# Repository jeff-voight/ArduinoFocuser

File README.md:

# ArduinoFocuser
My homemade Arduino Focuser

### Parts List
|ID				|#	|Name					|Type								|Module										|Description|
| ---			| ---	| ---					| ---								| ---										| ---										|
|A1				|1	|Arduino_UNO_R3			|MCU_Module:Arduino_UNO_R3			|Module:Arduino_UNO_R3						|Arduino UNO Microcontroller Module, release 3|
|C1, C2, C3		|3	|.01uF					|Device:C							|Capacitor_THT:C_Disc_D3.0mm_W2.0mm_P2.50mm	|Unpolarized capacitor|
|DRV1			|1	|Pololu_Breakout_DRV8825|Driver_Motor:Pololu_Breakout_DRV8825|Module:Pololu_Breakout-16_15.2x20.3mm		|Pololu Breakout Board, Stepper Driver DRV8825|
|Motor1			|1	|Stepper_Motor_bipolar	|Motor:Stepper_Motor_bipolar		|TerminalBlock:TerminalBlock_bornier-4_P5.08mm|4-wire bipolar stepper motor|
|R1, R2, R3, R4	|4	|10k					|Device:R							|Resistor_THT:R_Axial_DIN0204_L3.6mm_D1.6mm_P5.08mm_Horizontal|Resistor|
|SW1			|1	|Rotary_Encoder_Switch	|Device:Rotary_Encoder_Switch		|Rotary_Encoder:RotaryEncoder_Alps_EC11E-Switch_Vertical_H20mm|Rotary encoder, dual channel, incremental quadrate outputs, with switch|
|U1				|1	|DHT11					|Sensor:DHT11						|Sensor:Aosong_DHT11_5.5x12.0_P2.54mm		|Temperature and humidity module|
|U2				|1	|SN74HC14N				|dk_Logic-Gates-and-Inverters:SN74HC14N|digikey-footprints:DIP-14_W3mm			|IC INVERTER SCHMITT 6CH 14DIP|

* One (1) case of your choosing (plans for printing a sloppy case are included in the project)
* One (1) Motor mount (PDF somehwere around here for a 18ga steel bracket you can drill and bend yourself)
* One (1) coupler (I went with a 4mm x 6mm flexible coupler and drilled it to fit my shafts)
* One (1) 12VDC 2A power supply (wall-wart. You're just plugging it in to the Arduino UNOr3)
* Solder, wires, 4 pin connectors for as many scopes as you have.
* One long USB-A to USB-2 cable (or whatever the distance is from your laptop USB hub to where the focuser box will sit plus tripping slack)

# Things you'll want to change in the code:
My telescope focuser knob turns 5.75 times to go from end to end and moves some 13cm (or was it 23?). EncoderPositioner.h and StepperMotor.h are important.

For now, there may very-well be hardcoded values in the cpp files. I highly recommend you walk through them before applying bizarre amounts of
torque to your telescope focuser rod.

# To do:
* I want to add a limit switch to the motor end of the focus tube to detect the zero point. I haven't figured out how I want to impliment this. Maybe have the
focuser rack all the way closed on startup and then return to where it was. The problem I have with this is the people who have more than one telescope and 
maybe get the wiring wrong, causing their scope to rack focus out until it runs out of travel space and stalls the motor while seeking for the limit switch.

* Build a better case. For whatever reason, I can't get mine to close all the way and I'm pretty certain that I'm generating enough heat inside the box to affect
the DHT11 mounted on the side.

* Add links to a digikey BOM to order overthing.

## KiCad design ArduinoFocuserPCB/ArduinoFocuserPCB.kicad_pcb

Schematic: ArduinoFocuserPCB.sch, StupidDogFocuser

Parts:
A1: Arduino_UNO_R3
C1, C2, C3: .01uF; C_Disc_D3.0mm_W2.0mm_P2.50mm
DRV1: Pololu_Breakout_DRV8825; Pololu_Breakout-16_15.2x20.3mm
M1: Stepper_Motor_bipolar; TerminalBlock_bornier-4_P5.08mm
R1, R2, R3, R4: 10k; R_Axial_DIN0204_L3.6mm_D1.6mm_P5.08mm_Horizontal
SW1: Rotary_Encoder_Switch; RotaryEncoder_Alps_EC11E-Switch_Vertical_H20mm
U1: DHT11; Aosong_DHT11_5.5x12.0_P2.54mm
U2: SN74HC14N; DIP-14_W3mm; MPN SN74HC14N; Digi-Key_PN 296-1577-5-ND

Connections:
12V: A1.8 (VIN), C1.1, DRV1.8 (VMOT)
DHTIO: A1.28 (D13), U1.2 (IO)
Dir: A1.18 (D3), DRV1.16 (DIR)
ENCA: C2.2, R1.1, U2.5
ENCA_A: A1.20 (D5), U2.6
ENCB: C3.2, R4.1, U2.3
ENCB_A: A1.21 (D6), U2.4
Enable: A1.19 (D4), DRV1.9 (~EN)
GND: A1.6 (GND), A1.7 (GND), A1.29 (GND), C1.2, C2.1, C3.1, DRV1.1 (GND), DRV1.7 (GND), SW1.C, SW1.S2, U1.4 (GND), U2.7
M0: A1.14 (SCL/A5), DRV1.10 (M0)
M1: A1.13 (SDA/A4), DRV1.11 (M1)
M2: A1.12 (A3), DRV1.12 (M2)
unnamed 12: DRV1.3 (A2), M1.1; also elsewhere on the board
unnamed 13: DRV1.4 (A1), M1.2 (-); also elsewhere on the board
unnamed 14: DRV1.5 (B1), M1.3; also elsewhere on the board
unnamed 15: DRV1.6 (B2), M1.4; also elsewhere on the board
unnamed: R1.2, R2.2, SW1.A
unnamed: R3.2, R4.2, SW1.B
S1: SW1.S1, U2.1
S1_A: A1.24 (D9), U2.2
Step: A1.17 (D2), DRV1.15 (STEP)
VCC: A1.5 (+5V), DRV1.13 (~RST), DRV1.14 (~SLP), R2.1, R3.1, U1.1 (VCC), U2.14

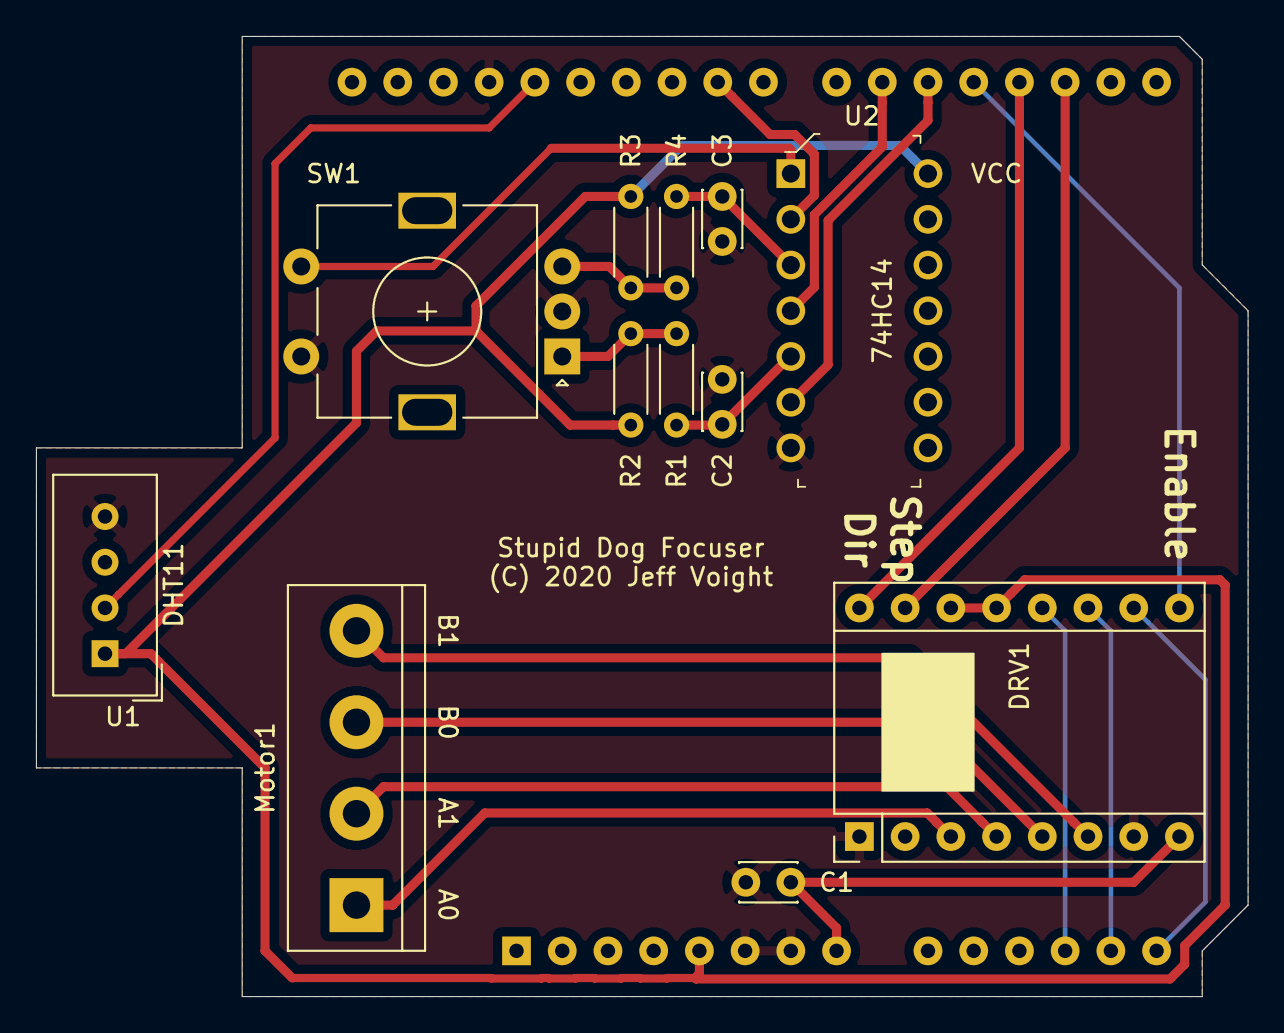
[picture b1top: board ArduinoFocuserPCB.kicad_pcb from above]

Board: 2 copper layers, 67.3 x 53.3 mm, 13 parts (1 on the bottom side), 22 nets.

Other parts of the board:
Motor1: Stepper_Motor_bipolar; TerminalBlock_bornier-4_P5.08mm

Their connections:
unnamed 12: Motor1.1; also elsewhere on the board
unnamed 13: Motor1.2; also elsewhere on the board
unnamed 14: Motor1.3; also elsewhere on the board
unnamed 15: Motor1.4; also elsewhere on the board

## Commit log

2016-04-12 Initial checkin
2016-04-12 Still initial
2016-04-14 Only missing limit setters and ASCOM drivers. Probably filled with bugs.
2016-04-16 Still have a cycling positioner bug
2016-04-17 Changed something. Lord knows what. Probably stepper stuff.
2016-04-18 ASCOM Driver and commands
2016-04-18 updated some ascom commands
2016-04-18 Added circuit diagram
2016-04-18 Added motor mount 3d printer models
2016-04-18 Added case diagrams for 3d printer
2016-04-18 Edited the readme to actually say something
2016-04-18 Formatting readme
2016-04-18 some file is missing
2016-04-18 Added a suspend so upon close, I can disconnect the motor.
2016-04-20 Added unsigned to the micros() and last micros()
2020-01-27 Revert "Added unsigned to the micros() and last micros()"
    This reverts commit c66d8b4b85dd3000e5163930f08a163de1e70bb6.
2020-02-02 checkpoint
2020-02-02 compiles.
2020-02-02 ammend
2020-02-02 remove some variables
2020-02-09 no clue.
2020-02-09 Unordered List
2020-02-09 comments and a little cleanup
2020-02-09 var cleaning and removing extraneous serial init.
2020-02-10 Accel working. LCD a mess
2020-02-11 created pcb files
2020-02-11 wired up
2020-02-11 created traces
2020-02-11 cleanup
2020-02-12 kicad
2020-02-12 'bak'
2020-02-12 better cleaning
2020-02-15 remove
2020-02-15 more conflicts
2020-02-15 trigger added. some routing. needed restart checkpoint
2020-02-15 git ignore
2020-02-15 readme checkpoint
2020-02-16 max speed 800, accel 200
2022-02-11 Bump Google.Protobuf in /ArduinoFocuser/VoightFocuserDriver
    Bumps [Google.Protobuf](https://github.com/protocolbuffers/protobuf) from 3.7.0 to 3.15.0.
    - [Release notes](https://github.com/protocolbuffers/protobuf/releases)
    - [Changelog](https://github.com/protocolbuffers/protobuf/blob/master/generate_changelog.py)
    - [Commits](https://github.com/protocolbuffers/protobuf/compare/v3.7.0...v3.15.0)
    ---
    updated-dependencies:
2022-06-22 Bump Newtonsoft.Json in /ArduinoFocuser/VoightFocuserDriver
    Bumps [Newtonsoft.Json](https://github.com/JamesNK/Newtonsoft.Json) from 10.0.3 to 13.0.1.
    - [Release notes](https://github.com/JamesNK/Newtonsoft.Json/releases)
    - [Commits](https://github.com/JamesNK/Newtonsoft.Json/compare/10.0.3...13.0.1)
    ---
    updated-dependencies:
    - dependency-name: Newtonsoft.Json
2026-01-21 Bump Newtonsoft.Json in /ArduinoFocuser/VoightFocuserDriver (#11)
    Bumps [Newtonsoft.Json](https://github.com/JamesNK/Newtonsoft.Json) from 10.0.3 to 13.0.1.
    - [Release notes](https://github.com/JamesNK/Newtonsoft.Json/releases)
    - [Commits](https://github.com/JamesNK/Newtonsoft.Json/compare/10.0.3...13.0.1)
    ---
    updated-dependencies:
    - dependency-name: Newtonsoft.Json

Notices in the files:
ArduinoFocuserPCB/ArduinoFocuserPCB.kicad_pcb:
(C) 2020 Jeff Voight
